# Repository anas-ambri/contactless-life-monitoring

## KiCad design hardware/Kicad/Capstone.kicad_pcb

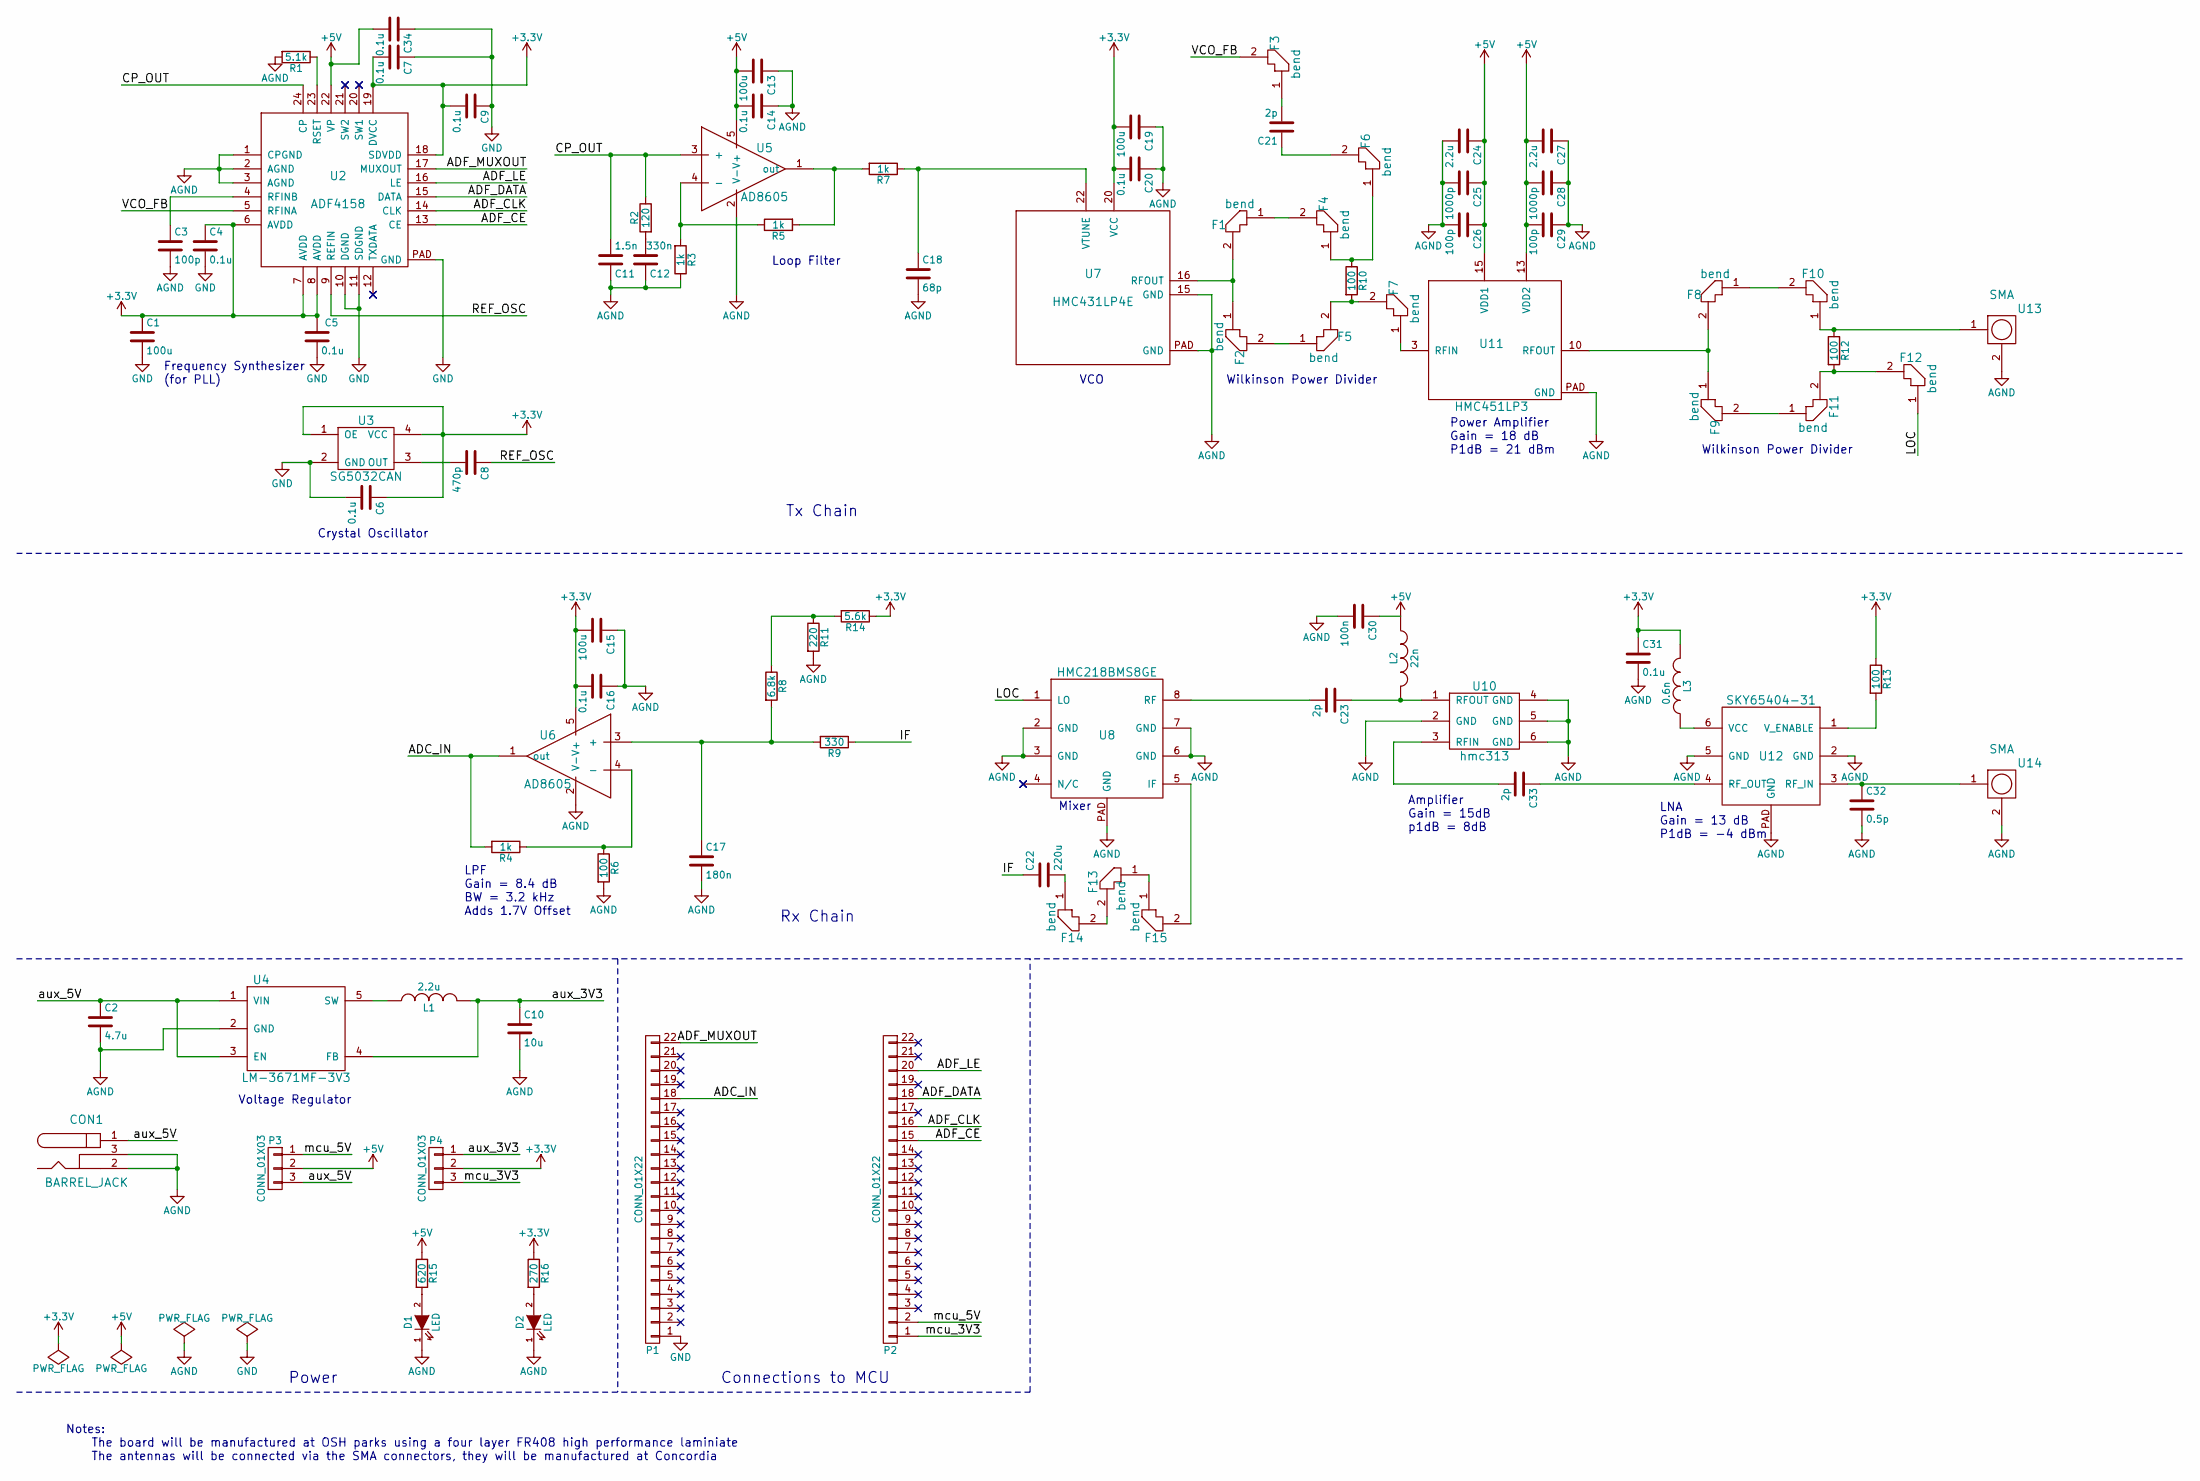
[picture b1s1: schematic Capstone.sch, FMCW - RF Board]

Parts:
C1, C13, C15, C19: 100u; C_1206
C2: 4.7u; C_0603
C3: 100p; C_0402
C4, C5, C6, C7, C9, C14, C16, C20, C31, C34: 0.1u; C_0805
C8: 470p; C_0805
C10: 10u; C_0805
C11: 1.5n; C_0805
C12: 330n; C_1206
C17: 180n; C_0603
C18: 68p; C_0603
C21, C23, C33: 2p; C_0402
C22: 220u; C_1206
C24, C27: 2.2u; C_0805
C25, C28: 1000p; C_0805
C26, C29: 100p; C_0805
C30: 100n; C_0805
C32: 0.5p; C_0402
CON1: BARREL_JACK
D1, D2: LED; LED_0603
F1, F2, F4, F5, F8, F9, F10, F11: bend; miter_0.17_90
F3, F6, F7, F12, F13, F14, F15: bend; miter_0.34_90
L1: 2.2u; R_0603
L2: 22n; R_0402
L3: 0.6n; R_0402
P1, P2: CONN_01X22; CONN_1x22
P3, P4: CONN_01X03; PWR_exchange
R1: 5.1k; R_0603
R2: 120; R_0603
R3, R4, R5, R7: 1k; R_0805
R6, R10, R12, R13: 100; R_0603
R8: 6.8k; R_0603
R9: 330; R_0603
R11: 220; R_0603
R14: 5.6k; R_0603
R15: 620; R_0603
R16: 270; R_0603
U2: ADF4158; 24-WFQFN
U3: SG5032CAN; 4-SMD
U4: LM-3671MF-3V3; SOT-23-5
U5, U6: AD8605; SOT-23-5
U7: HMC431LP4E; 24-QFN
U8: HMC218BMS8GE; MSOP-8
U10: hmc313; SOT23-6
U11: HMC451LP3; 16-QFN
U12: SKY65404-31; 6-QFN
U13, U14: SMA

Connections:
+3V3: C1.1, C4.1, C5.1, C6.1, C7.2, C9.2, C15.2, C16.2, C19.2, C20.2, C31.1, L3.2, P4.2, R13.1, R14.1, R16.1, U2.6 (AVDD), U2.7 (AVDD), U2.8 (AVDD), U2.18 (SDVDD), U2.19 (DVCC), U3.1 (OE), U3.4 (VCC), U6.5 (V+), U7.20 (VCC)
+5V: C13.2, C14.2, C24.1, C25.1, C26.1, C27.2, C28.2, C29.2, C30.1, C34.2, L2.1, P3.2, R15.1, U2.22 (VP), U5.5 (V+), U11.13 (VDD2), U11.15 (VDD1)
/ADC_IN: P1.18, R4.2, U6.1 (out)
/ADF_CE: P2.15, U2.13 (CE)
/ADF_CLK: P2.16, U2.14 (CLK)
/ADF_DATA: P2.18, U2.15 (DATA)
/ADF_LE: P2.20, U2.16 (LE)
/ADF_MUXOUT: P1.22, U2.17 (MUXOUT)
/CP_OUT: C11.2, R2.1, U2.24 (CP), U5.3 (+)
/IF: C22.1, R9.1
/LOC: F12.1, U8.1 (LO)
/REF_OSC: C8.1, U2.9 (REFIN)
/VCO_FB: F3.2, U2.5 (RFINA)
/aux_3V3: C10.1, L1.2, P4.1, U4.4 (FB)
/aux_5V: C2.1, CON1.1, P3.3, U4.1 (VIN), U4.3 (EN)
/mcu_3V3: P2.1, P4.3
/mcu_5V: P2.2, P3.1
GND: C1.2, C4.2, C5.2, C6.2, C7.1, C9.1, C34.1, P1.1, U2.10 (DGND), U2.11 (SDGND), U2.PAD (GND), U3.2 (GND)
GNDA: C2.2, C3.2, C10.2, C11.1, C12.1, C13.1, C14.1, C15.1, C16.1, C17.2, C18.2, C19.1, C20.1, C24.2, C25.2, C26.2, C27.1, C28.1, C29.1, C30.2, C31.2, C32.2, CON1.2, CON1.3, D1.1 (K), D2.1 (K), R1.2, R3.1, R6.2, R11.2, U2.1 (CPGND), U2.2 (AGND), U2.3 (AGND), U4.2 (GND), U5.2 (V-), U6.2 (V-), U7.15 (GND), U7.PAD (GND), U8.2 (GND), U8.3 (GND), U8.6 (GND), U8.7 (GND), U8.PAD (GND), U10.2 (GND), U10.4 (GND), U10.5 (GND), U10.6 (GND), U11.PAD (GND), U12.2 (GND), U12.5 (GND), U12.PAD (GND), U13.2, U14.2
unnamed: C3.1, U2.4 (RFINB)
unnamed: C8.2, U3.3 (OUT)
unnamed: C12.2, R2.2
unnamed: C17.1, R8.2, R9.2, U6.3 (+)
unnamed: C18.1, R7.1, U7.22 (VTUNE)
unnamed: C21.1, F6.2
unnamed: C21.2, F3.1
unnamed: C22.2, F14.1
unnamed: C23.1, L2.2, U10.1 (RFOUT)
unnamed: C23.2, U8.8 (RF)
unnamed: C32.1, U12.3 (RF_IN), U14.1
unnamed: C33.1, U12.4 (RF_OUT)
unnamed: C33.2, U10.3 (RFIN)
unnamed: D1.2 (A), R15.2
unnamed: D2.2 (A), R16.2
unnamed: F1.1, F4.2
unnamed: F1.2, F2.1, U7.16 (RFOUT)
unnamed: F2.2, F5.1
unnamed: F4.1, F6.1, R10.1
unnamed: F5.2, F7.2, R10.2
unnamed: F7.1, U11.3 (RFIN)
unnamed: F8.2, F9.1, U11.10 (RFOUT)
unnamed: F10.1, R12.1, U13.1
unnamed: F8.1, F10.2
unnamed: F9.2, F11.1
unnamed: F11.2, F12.2, R12.2
unnamed: F13.1, F15.1
unnamed: F13.2, F14.2
unnamed: F15.2, U8.5 (IF)
unnamed: L1.1, U4.5 (SW)
unnamed: L3.1, U12.6 (VCC)
unnamed: R1.1, U2.23 (RSET)
unnamed: R3.2, R5.1, U5.4 (-)
unnamed: R4.1, R6.1, U6.4 (-)
unnamed: R5.2, R7.2, U5.1 (out)
unnamed: R8.1, R11.1, R14.2
unnamed: R13.2, U12.1 (V_ENABLE)

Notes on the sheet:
Mixer
VCO
Frequency Synthesizer (for PLL)
Wilkinson Power Divider
LNA Gain = 13 dB P1dB = -4 dBm
LPF Gain = 8.4 dB BW = 3.2 kHz Adds 1.7V Offset
Power Amplifier Gain = 18 dB P1dB = 21 dBm
Notes: The board will be manufactured at OSH parks using a four layer FR408 high performance laminiate The antennas will be connected via the SMA connectors, they will be manufactured at Concordia
Loop Filter
Crystal Oscillator
Voltage Regulator
Tx Chain
Rx Chain
Power
Connections to MCU
Amplifier Gain = 15dB p1dB = 8dB

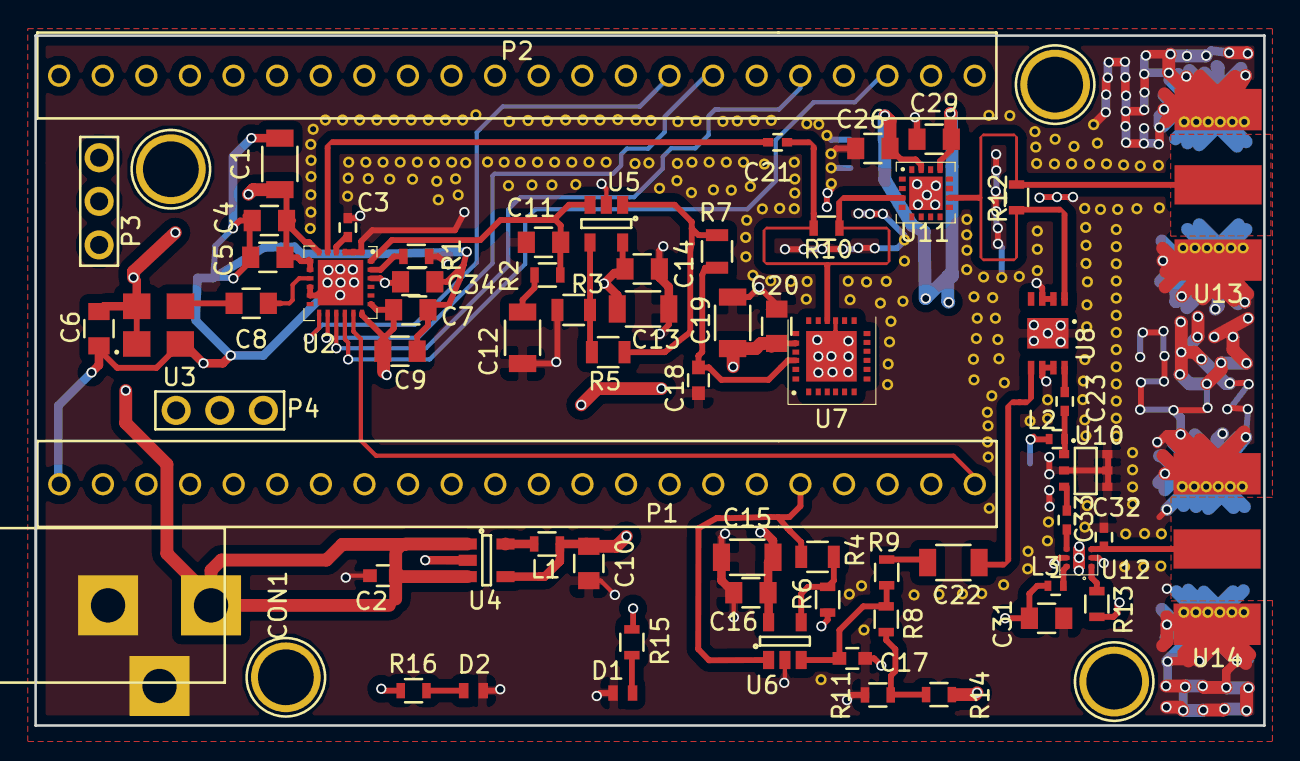
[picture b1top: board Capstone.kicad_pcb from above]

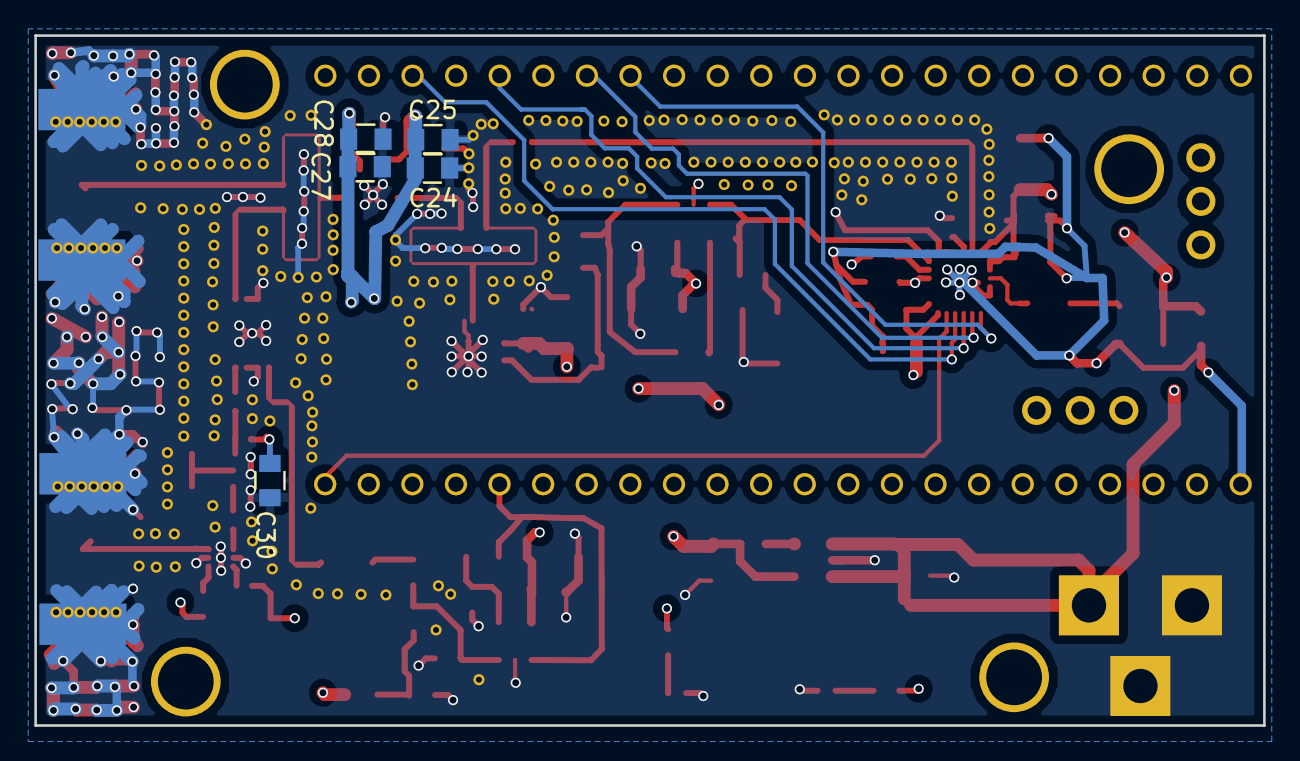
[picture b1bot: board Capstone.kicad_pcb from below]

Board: 4 copper layers, 71.6 x 40.2 mm, 87 parts (5 on the bottom side), 56 nets.

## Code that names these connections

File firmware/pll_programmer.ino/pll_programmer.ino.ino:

#include "TimerOne.h"

int ADF_CLK = 2;
int ADF_LE = 4;
int ADF_CE = 7;
int ADF_DATA = 8;
int ADF_MUXOUT = 12;

extern TimerOne Timer1;

#define DEBUG 1
bool muxout = true;
bool LESetup = false;

unsigned long R7, R6_1, R6_2, R5_1, R5_2, R4, R3, R2, R1, R0, FLAG;

const int MAX_BITS = 32;
const int NUM_REGS = 10;
int counter_clk_break = 2;
int counterBit = MAX_BITS -1; //31 because 0-indexed
int counter = 0;
unsigned long regs[NUM_REGS];

void setup() {
  Serial.begin(9600);
  // put your setup code here, to run once:
  pinMode(ADF_CLK, OUTPUT);
  pinMode(ADF_LE, OUTPUT);
  pinMode(ADF_CE, OUTPUT);
  pinMode(ADF_DATA, OUTPUT);
  pinMode(ADF_MUXOUT, INPUT);

  Timer1.initialize(1000); //2us, 500KHz frequency
  Timer1.attachInterrupt(callback);

  R7 = 7; //00000000000000000000000000000111
  R6_1 = 200006; //00000000000000110000110101000110;
  R6_2 = 8588614;//00000000100000110000110101000110;

  if (muxout) {
    R5_1 = 100727725; //00000110000000001111101110101101
    R5_2 = 109116333; //00000110100000001111101110101101;
  } else {
    R5_1 = 134282157; //00001000000000001111101110101101;
    R5_2 = 142670765; //00001000100000001111101110101101;    
  }

  if (muxout) {
    R4 = 5767300; //00000001100001100000000010000100;
  } else {
    R4 = 26738820; //00000001100110000000000010000100;
  }

  R3 = 32835; //00000000000000001000000001100011;
  R2 = 255885330; //00001111010000001000000000010010;
  R1 = 1;//00000000000000000000000000000001;2

  if (muxout) {
    R0 = 4168253440; //11111000011100101000000000000000;
  } else {
    R0 = 2154987520; //10000000011100101000000000000000;
  }
  //FLAG = 0;
  
  regs[0] = R7;
  regs[1] = R6_1;
  regs[2] = R6_2;
  regs[3] = R5_1;
  regs[4] = R5_2;
  regs[5] = R4;
  regs[6] = R3;
  regs[7] = R2;
  regs[8] = R1;
  regs[9] = R0;
//  #ifdef DEBUG
//  regs[10] = FLAG;
//  regs[11] = FLAG;
//  #endif

  digitalWrite(ADF_CE, HIGH);
  digitalWrite(ADF_LE, HIGH);
}

void callback() {
  digitalWrite(ADF_LE, LOW);
  
  if (counter_clk_break > 0) {
    counter_clk_break--;
    if(counter_clk_break == 2){
      digitalWrite(ADF_DATA, HIGH);
    }

    if(counter_clk_break == 1) {
      digitalWrite(ADF_DATA, LOW);
    }
  } else {
  
    //Get the state of the CLK
    //(whether it is up or down)
    bool clk_Pin = digitalRead(ADF_CLK);
  
    //Toggle the clock
    digitalWrite(ADF_CLK, clk_Pin ^ 1);
    
    //If the rising edge of the clock
    if(clk_Pin) {
      
      if (counter < NUM_REGS) {
  
        if(counterBit == MAX_BITS -1) {
          digitalWrite(ADF_LE, LOW);
        }
    
        //Write bit at position counterBit in the register
        
        digitalWrite(ADF_DATA, (regs[counter] >> (counterBit)) & 1);
  
        //Move to the next bit
        counterBit--;
  
      }
    } else {
  
        //If we got to the last bit on the register
        if (counterBit < 0) {
          //we need to set LE to high
          digitalWrite(ADF_LE, HIGH);
          
          //Reset the position of the bit counter
          counterBit = MAX_BITS -1;
          //Move to the next register
          counter++;

          //Finished writing 
          //We are now in counter_clk_break mode
          if(counter == NUM_REGS) {
            //counter_clk_break > 0 means we are on clk_break mode
            counter_clk_break = MAX_BITS - 1;
          }

        }

        //We are now in readback mode
        if(counter_clk_break == 0) {
          Serial.write(digitalRead(ADF_MUXOUT));
        }
    }
    
  }
  
  
}

void loop() {
  // put your main code here, to run repeatedly:

}

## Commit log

2015-12-07 2nd commit
    all source files as of Nov 30th, 2015
2015-12-25 Move /Icons /src to /UI
2015-12-25 Add docs for lpcxpresso, xplorer
2016-02-07 Adding windows drivers
2016-02-07 Add usb basic project
2016-02-09 Add host code
2016-02-11 Update with pyusb info
2016-02-11 Rename README.txt to README.md
2016-02-12 Added non-optimal rate range test for color warning
2016-02-12 Added basic static path, still need to optimize sample batch sizes
2016-02-14 Rename hid_main into main, added logic for collecting data from ADC
2016-02-15 Added PLL programming
2016-02-15 Fix LED flash
2016-02-22 Add file with weird voltages off pins
2016-02-25 Weird voltages
2016-02-25 Modified part of UI using gif icons,behaviour not complete.Algo still to extract rates
2016-03-04 UI complete pending proper exit function realization, algo- periodicity test + extraction pending
2016-03-10 Added python program that creates 2 way communication with board. Missing: controlling data being sent
2016-03-11 Periodicity test complete,execution time test pending, extraction pending
2016-03-15 program LPC
2016-03-17 Logic to enable debug mode
2016-03-17 Uncomment USB & ADC
2016-03-18 Change program to send data continuously, change host to read it
2016-03-20 Add antenna design files
2016-03-20 Remove object files
2016-03-21 Add hardware folder
2016-03-22 no significant changes
2016-03-23 Send byte
2016-03-23 no sig changes 21:07 22/03/2016
2016-03-23 Save 100ms of data in array
2016-03-24 Changing code to send in bulk
2016-03-26 New version of program to collect data with isochronous, every 2 ms
2016-03-26 Add test data collected with isochronous
2016-03-26 Add release build images
2016-03-29 Added final version for demo day
2016-03-30 Updated algorithm
2016-03-30 Remove object files for release
2016-03-30 Add get_next function
2016-03-30 Added v3 version
